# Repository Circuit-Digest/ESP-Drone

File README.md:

# ESP-Drone

<br>

<br>

For a full tutorial check out our [ESP32 Drone Article](https://circuitdigest.com/microcontroller-projects/DIY-wifi-controlled-drone).
For working video:  [How to build an ESP32 Drone](https://youtu.be/uzZjk0TQKtU).

This project is a custom-built drone powered by an ESP32 microcontroller. It’s designed as a lightweight and affordable platform to explore flight dynamics, motor control, and real-time sensor integration.

The goal was to understand how a drone balances, responds to movement, and maintains stability using onboard sensors and code logic. It’s a hands-on way to learn about embedded systems and control loops while building something practical and fun.

The repository includes all the core files — code, wiring references, and setup details — so others can learn from or build upon it.

Drones have rapidly evolved from niche hobbies to versatile tools with a wide range of applications, from photography to agriculture or even for defense and military purposes. Depending on the application, features and payload capacity their price will vary from pocket changes to a few million. Even though the basic principle behind these drones may appear simple, there is a lot of technology and computation that goes behind it for proper operations and a desired result from these drones. For example, maintaining stability while in the air requires precision sensors such as a Gyroscope and proper processing of reading taken with it. In this project we are going to make such a drone which can be easily controlled using our phones.
This DIY drone is small in size and can be built using easily available components such as ESP32 modules, MPU6050 IMU, coreless motors and plastic propellers.

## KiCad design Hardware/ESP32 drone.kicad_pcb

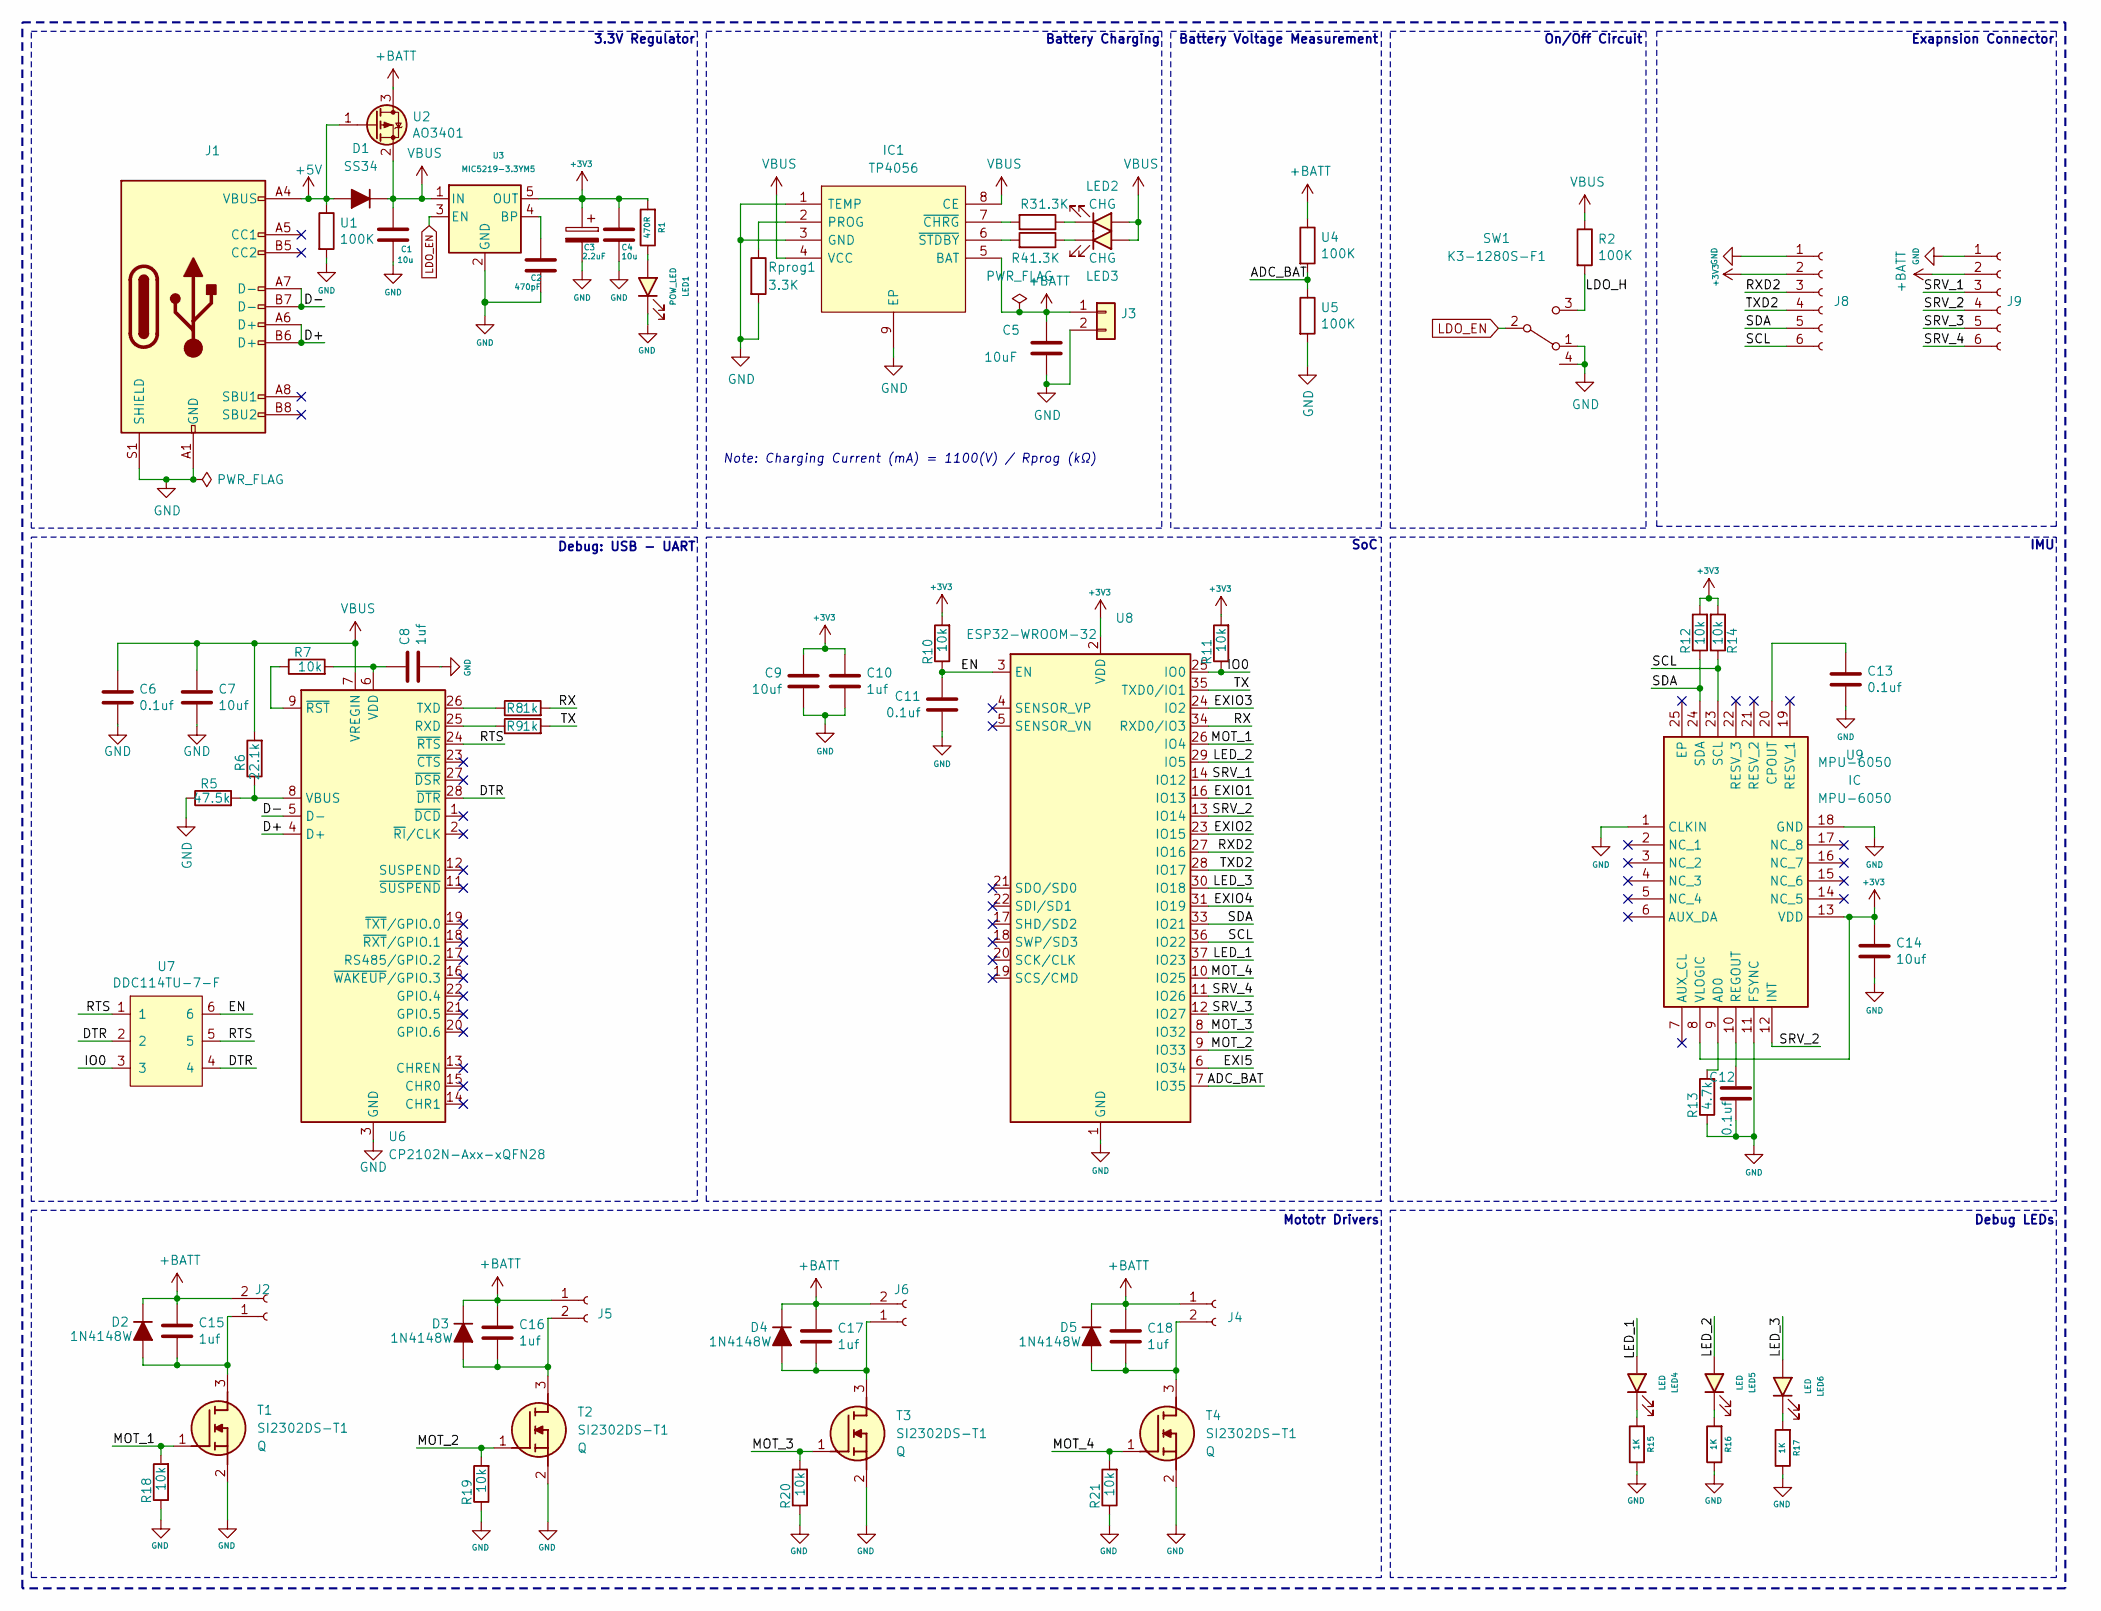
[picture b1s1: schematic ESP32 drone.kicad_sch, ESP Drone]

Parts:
C1, C4: 10u; C_0603_1608Metric
C2: 470pF; C_0603_1608Metric
C3: 2.2uF; C_0805_2012Metric
C5: 10uF; C_0603_1608Metric
C6, C11, C12, C13: 0.1uf; C_0603_1608Metric
C7, C9, C14: 10uf; C_0603_1608Metric
C8, C10, C15, C16, C17, C18: 1uf; C_0603_1608Metric
D1: SS34; D_SMA
D2, D3, D4, D5: 1N4148W; D_SOD-323
IC1: TP4056; SOIC127P600X175-9N; Manufacturer_Part_Number TP4056-42-ESOP8
J1: USB_C_Receptacle_USB2.0; USB_C_Receptacle_HRO_TYPE-C-31-M-12
J2, J4, J5, J6: Conn_01x02_Female; JST_GH_SM02B-GHS-TB_1x02-1MP_P1.25mm_Horizontal
J3: B2B-PH-SM4-TB(LF)(SN); JST_PH_B2B-PH-SM4-TB_1x02-1MP_P2.00mm_Vertical
J8, J9: Conn_01x06_Female; PinHeader_1x06_P2.54mm_Vertical
LED1: POW_LED; LED_0603_1608Metric
LED2, LED3: CHG; LED_0603_1608Metric
LED4, LED5, LED6: LED; LED_0603_1608Metric
R1: 470R; R_0603_1608Metric
R2: 100K; R_0603_1608Metric
R3, R4: 1.3K; R_0603_1608Metric
R5: 47.5k; R_0603_1608Metric
R6: 22.1k; R_0603_1608Metric
R7, R10, R11, R12, R14, R18, R19, R20, R21: 10k; R_0603_1608Metric
R8, R9: 1k; R_0603_1608Metric
R13: 4.7k; R_0603_1608Metric
R15, R16, R17: 1K; R_0603_1608Metric
Rprog1: 3.3K; R_0603_1608Metric
SW1: K3-1280S-F1; slide switch spdt
T1, T2, T3, T4: SI2302DS-T1; SOT95P237X112-3N; Mouser Part Number 781-SI2302DS
U1, U4, U5: 100K; R_0603_1608Metric
U2: AO3401; SOT-23
U3: MIC5219-3.3YM5; SOT-23-5
U6: CP2102N-Axx-xQFN28; QFN-28-1EP_5x5mm_P0.5mm_EP3.35x3.35mm
U7: DDC114TU-7-F; SOT-363_SC-70-6
U8: ESP32-WROOM-32
U9: MPU-6050; MPU6050; Mouser Part Number 410-MPU-6050

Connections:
+3V3: C3.1, C4.1, C9.1, C10.1, C14.1, J8.2, R1.2, R10.2, R11.2, R12.2, R14.2, U3.5 (OUT), U8.2 (VDD), U9.8 (VLOGIC), U9.13 (VDD)
+5V: D1.2 (A), J1.A4 (VBUS), J1.A9 (VBUS), J1.B4 (VBUS), J1.B9 (VBUS), U1.1, U2.1 (G)
+BATT: C5.1, C15.1, C16.1, C17.1, C18.1, D2.1 (K), D3.1 (K), D4.1 (K), D5.1 (K), IC1.5 (BAT), J2.2, J3.1, J4.1, J5.1, J6.2, J9.2, U2.3 (D), U4.1
/ADC_BAT: U4.2, U5.1, U8.7 (IO35)
/D+: J1.A6 (D+), J1.B6 (D+), U6.4 (D+)
/D-: J1.A7 (D-), J1.B7 (D-), U6.5 (D-)
/DTR: U6.28 (~DTR), U7.2, U7.4
/EN: C11.1, R10.1, U7.6, U8.3 (EN)
/EXI5: U8.6 (IO34)
/EXIO1: U8.16 (IO13)
/EXIO2: U8.23 (IO15)
/EXIO3: U8.24 (IO2)
/EXIO4: U8.31 (IO19)
/IO0: R11.1, U7.3, U8.25 (IO0)
/LDO_H: R2.2, SW1.3 (C)
/LED_1: LED4.2 (A), U8.37 (IO23)
/LED_2: LED5.2 (A), U8.29 (IO5)
/LED_3: LED6.2 (A), U8.30 (IO18)
/MOT_1: R18.2, T1.1 (G), U8.26 (IO4)
/MOT_2: R19.2, T2.1 (G), U8.9 (IO33)
/MOT_3: R20.2, T3.1 (G), U8.8 (IO32)
/MOT_4: R21.2, T4.1 (G), U8.10 (IO25)
/RTS: U6.24 (~RTS), U7.1, U7.5
/RX: R8.2, U8.34 (RXD0/IO3)
/RXD2: J8.3, U8.27 (IO16)
/SCL: J8.6, R14.1, U8.36 (IO22), U9.23 (SCL)
/SDA: J8.5, R12.1, U8.33 (IO21), U9.24 (SDA)
/SRV_1: J9.3, U8.14 (IO12)
/SRV_2: J9.4, U8.13 (IO14), U9.12 (INT)
/SRV_3: J9.5, U8.12 (IO27)
/SRV_4: J9.6, U8.11 (IO26)
/TX: R9.2, U8.35 (TXD0/IO1)
/TXD2: J8.4, U8.28 (IO17)
GND: C1.2, C2.2, C3.2, C4.2, C5.2, C6.2, C7.2, C8.2, C9.2, C10.2, C11.2, C12.2, C13.2, C14.2, IC1.1 (TEMP), IC1.3 (GND), IC1.9 (EP), J1.A1 (GND), J1.A12 (GND), J1.B1 (GND), J1.B12 (GND), J1.S1 (SHIELD), J3.2, J8.1, J9.1, LED1.1 (K), R5.1, R13.1, R15.1, R16.1, R17.1, R18.1, R19.1, R20.1, R21.1, Rprog1.2, SW1.1 (A), SW1.4, T1.2 (S), T2.2 (S), T3.2 (S), T4.2 (S), U1.2, U3.2 (GND), U5.2, U6.3 (GND), U6.29 (GND), U8.1 (GND), U8.15 (GND), U8.38 (GND), U8.39 (GND), U9.1 (CLKIN), U9.11 (FSYNC), U9.18 (GND)
LDO_EN: SW1.2 (B), U3.3 (EN)
unnamed: C15.2, D2.2 (A), J2.1, T1.3 (D)
unnamed: C16.2, D3.2 (A), J5.2, T2.3 (D)
unnamed: C17.2, D4.2 (A), J6.1, T3.3 (D)
unnamed: C18.2, D5.2 (A), J4.2, T4.3 (D)
unnamed: IC1.2 (PROG), Rprog1.1
unnamed: IC1.7 (~CHRG), R3.2
unnamed: IC1.6 (~STDBY), R4.2
unnamed: LED1.2 (A), R1.1
unnamed: LED2.1 (K), R3.1
unnamed: LED3.1 (K), R4.1
unnamed: LED4.1 (K), R15.2
unnamed: LED5.1 (K), R16.2
unnamed: LED6.1 (K), R17.2
unnamed: C2.1, U3.4 (BP)
unnamed: R9.1, U6.25 (RXD)
unnamed: R8.1, U6.26 (TXD)
unnamed: R5.2, R6.1, U6.8 (VBUS)
unnamed: C8.1, R7.2, U6.6 (VDD)
unnamed: R7.1, U6.9 (~RST)
unnamed: R13.2, U9.9 (AD0)
unnamed: C13.1, U9.20 (CPOUT)
unnamed: C12.1, U9.10 (REGOUT)
VBUS: C1.1, C6.1, C7.1, D1.1 (K), IC1.4 (VCC), IC1.8 (CE), LED2.2 (A), LED3.2 (A), R2.1, R6.2, U2.2 (S), U3.1 (IN), U6.7 (VREGIN)

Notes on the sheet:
SoC
Battery Voltage Measurement
IMU
Mototr Drivers
Battery Charging
Debug LEDs
Debug: USB - UART
Exapnsion Connector
3.3V Regulator
Note: Charging Current (mA) = 1100(V) / Rprog (kΩ)
On/Off Circuit

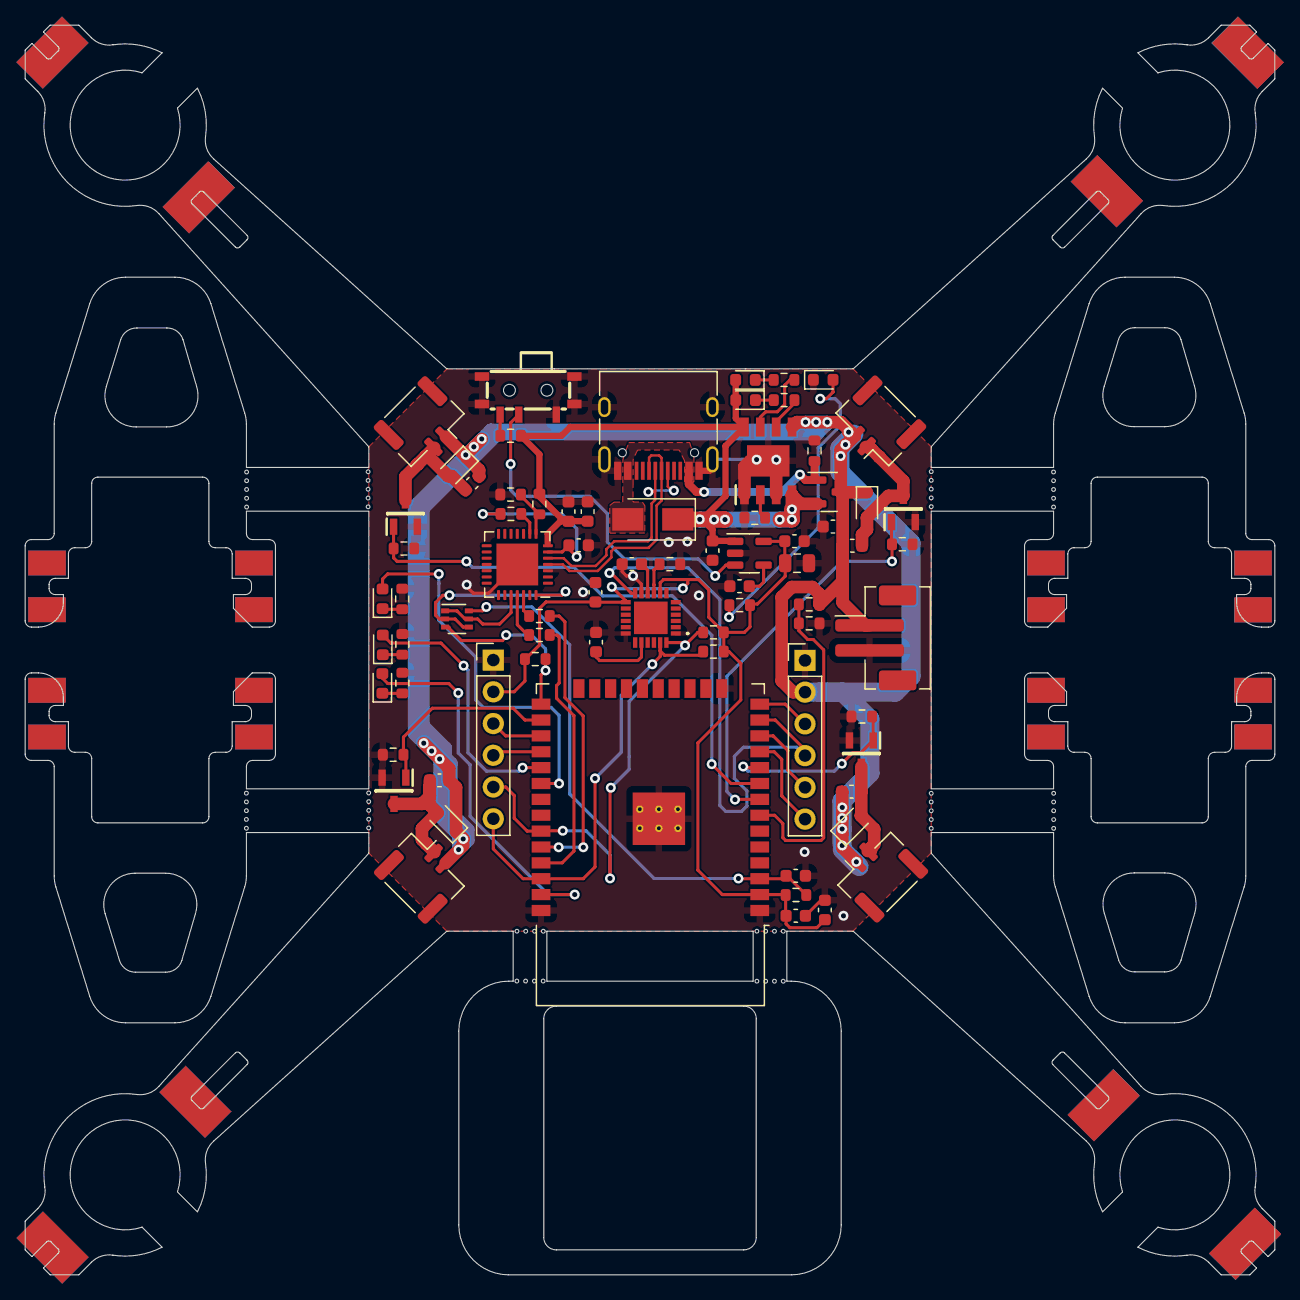
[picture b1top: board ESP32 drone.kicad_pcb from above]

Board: 2 copper layers, 100.0 x 100.0 mm, 74 parts (0 on the bottom side), 53 nets.

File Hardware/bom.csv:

Designator,Footprint,Quantity,Value,LCSC Part #
"C1, C4",603,2,10u,
"C10, C15, C16, C17, C18, C8",603,6,1uf,
"C11, C12, C13, C6",603,4,0.1uf,
"C14, C5, C7, C9",603,4,10uf,
C2,603,1,470pF,
C3,805,1,2.2uF,
D1,D_SMA,1,SS34,
"D2, D3, D4, D5",D_SOD-323,4,1N4148W,
IC1,SOIC127P600X175-9N,1,TP4056,
J1,USB_C_Receptacle_HRO_TYPE-C-31-M-12,1,USB_C_Receptacle_USB2.0,
"J2, J4, J5, J6",JST_GH_SM02B-GHS-TB_1x02-1MP_P1.25mm_Horizontal,4,Conn_01x02_Female,
J3,JST_PH_B2B-PH-SM4-TB_1x02-1MP_P2.00mm_Vertical,1, B2B-PH-SM4-TB(LF)(SN) ,
"J8, J9",PinHeader_1x06_P2.54mm_Vertical,2,Conn_01x06_Female,
LED1,603,1,POW_LED,
"LED2, LED3",603,2,CHG,
"LED4, LED5, LED6",603,3,LED,
R1,603,1,470R,
"R10, R11, R12, R14, R18, R19, R20, R21, R7",603,9,10k,
R13,603,1,4.7k,
"R15, R16, R17, R8, R9",603,5,1K,
"R2, U1, U4, U5",603,4,100K,
"R3, R4",603,2,1.3K,
R5,603,1,47.5k,
R6,603,1,22.1k,
Rprog1,603,1,3.3K,
SW1,slide switch spdt,1,K3-1280S-F1 ,
"T1, T2, T3, T4",SOT95P237X112-3N,4,SI2302DS-T1,
U2,SOT-23,1,AO3401,
U3,SOT-23-5,1,MIC5219-3.3YM5,
U6,QFN-28-1EP_5x5mm_P0.5mm_EP3.35x3.35mm,1,CP2102N-Axx-xQFN28,
U7,SOT-363_SC-70-6,1,2N7002D,
U8,ESP32-WROOM-32,1,ESP32-WROOM-32,
U9,MPU6050,1,MPU-6050,

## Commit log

2023-09-11 Create j
2025-03-20 Removed "acs.cmd"
    Identified threat https://www.virustotal.com/gui/file/c8f9ce3e4d55d1cf9b530d7cfb26da8dfae1f4b11dd7f7b1be71bead5e14aec0?nocache=1
    There are also minor detections in the binary files in the repository. I would suggest the poster to do a full virus scan, as their development machine may be compromised.
2025-10-17 Initial commit with offline changes
